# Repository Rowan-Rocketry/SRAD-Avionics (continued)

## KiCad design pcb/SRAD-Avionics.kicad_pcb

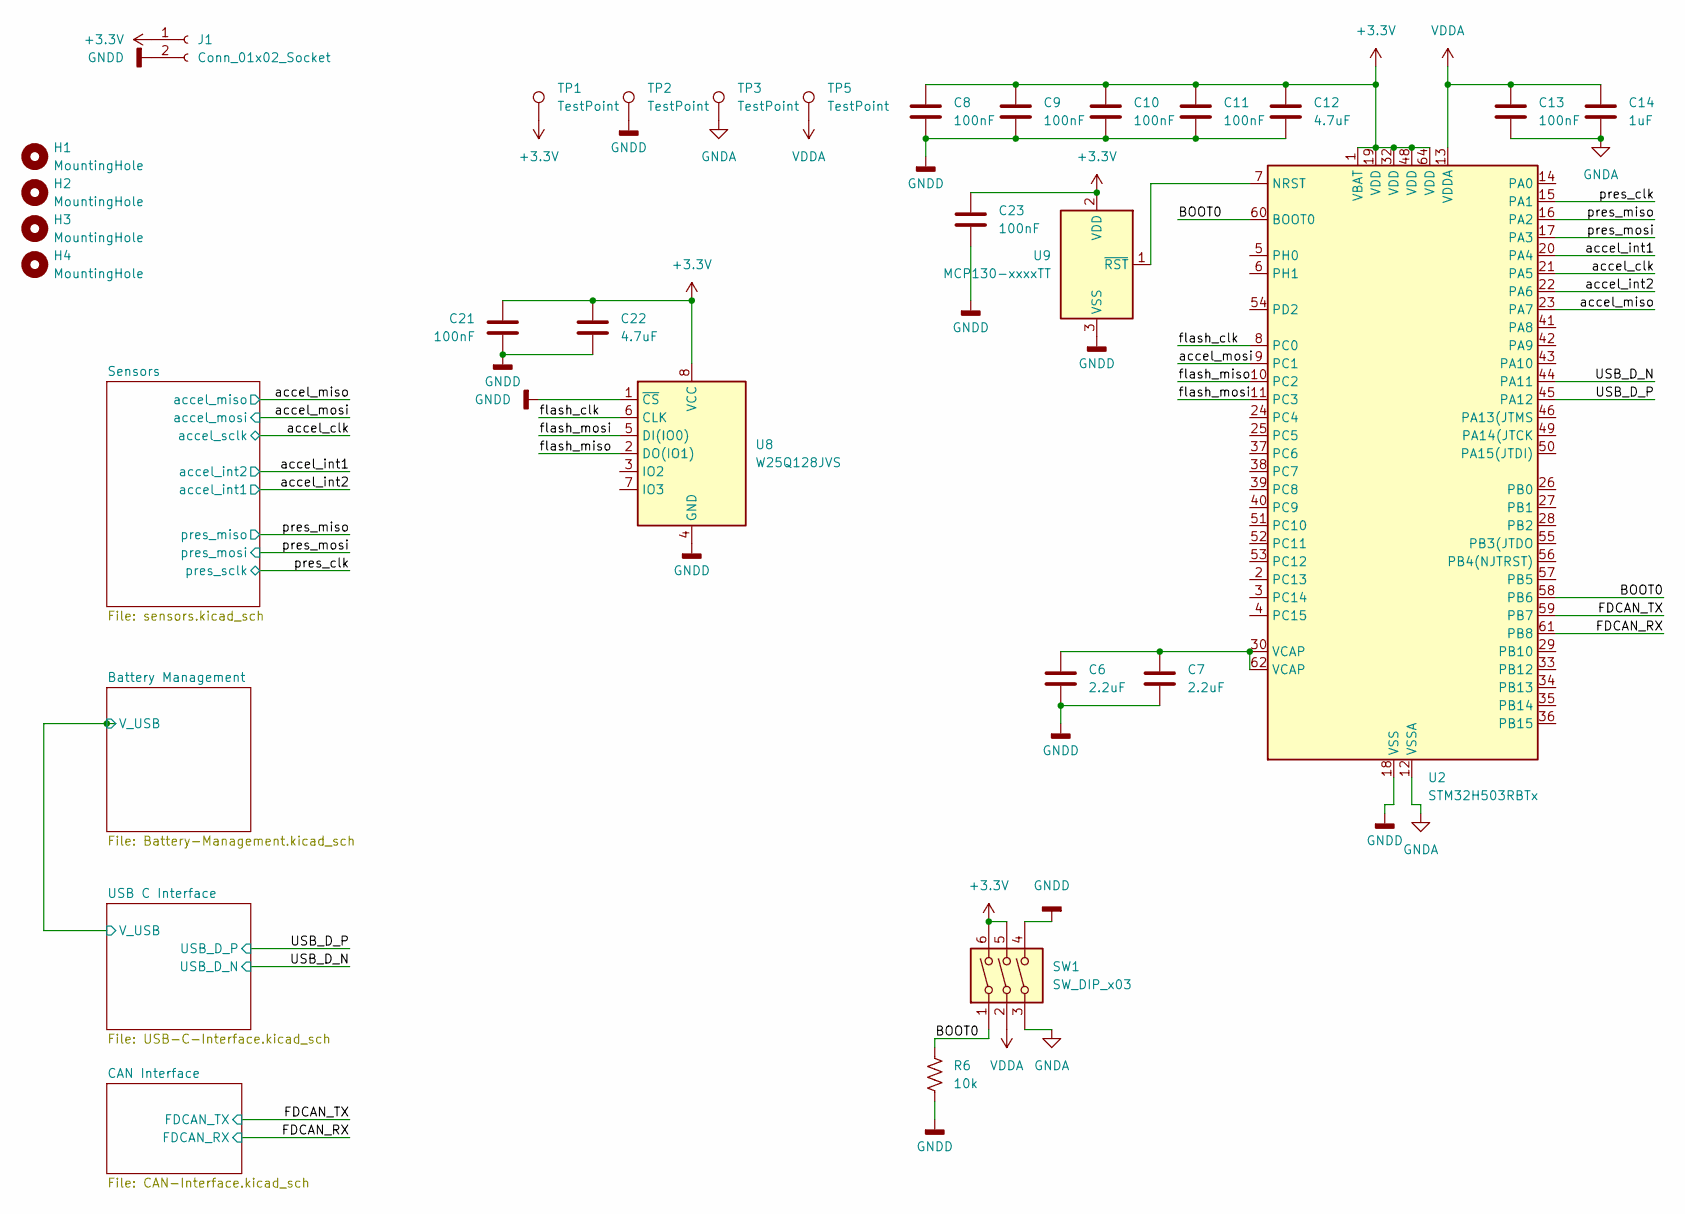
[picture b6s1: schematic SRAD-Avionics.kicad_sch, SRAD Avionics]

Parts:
C6, C7: 2.2uF; C_0603_1608Metric_Pad1.08x0.95mm_HandSolder
C8, C9, C10, C11, C13, C21, C23: 100nF; C_0603_1608Metric_Pad1.08x0.95mm_HandSolder
C12, C22: 4.7uF; C_0603_1608Metric_Pad1.08x0.95mm_HandSolder
C14: 1uF; C_0603_1608Metric_Pad1.08x0.95mm_HandSolder
H1, H2, H3, H4: MountingHole; MountingHole_3.2mm_M3
J1: Conn_01x02_Socket; TerminalBlock_Phoenix_MKDS-1,5-2-5.08_1x02_P5.08mm_Horizont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
R6: 10k; R_0603_1608Metric_Pad0.98x0.95mm_HandSolder
SW1: SW_DIP_x03; SW_DIP_SPSTx03_Slide_9.78x9.8mm_W7.62mm_P2.54mm
TP1, TP2, TP3, TP5: TestPoint; TestPoint_Loop_D2.60mm_Drill1.6mm_Beaded
U2: STM32H503RBTx; LQFP-64_10x10mm_P0.5mm
U8: W25Q128JVS; SOIC-8_5.23x5.23mm_P1.27mm
U9: MCP130-xxxxTT; SOT-23

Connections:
+3.3V: C8.1, C9.1, C10.1, C11.1, C12.1, C21.1, C22.1, C23.1, J1.1, SW1.5, SW1.6, TP1.1, U2.1 (VBAT), U2.19 (VDD), U2.32 (VDD), U2.48 (VDD), U2.64 (VDD), U8.8 (VCC), U9.2 (VDD); also elsewhere on the board
/BOOT0: R6.1, SW1.1, U2.58 (PB6), U2.60 (BOOT0)
/FDCAN_RX: U2.61 (PB8); also elsewhere on the board
/FDCAN_TX: U2.59 (PB7); also elsewhere on the board
/USB_D_N: U2.44 (PA11); also elsewhere on the board
/USB_D_P: U2.45 (PA12); also elsewhere on the board
/accel_clk: U2.21 (PA5); also elsewhere on the board
/accel_int1: U2.20 (PA4); also elsewhere on the board
/accel_int2: U2.22 (PA6); also elsewhere on the board
/accel_miso: U2.23 (PA7); also elsewhere on the board
/accel_mosi: U2.9 (PC1); also elsewhere on the board
/flash_clk: U2.8 (PC0), U8.6 (CLK)
/flash_miso: U2.10 (PC2), U8.2 (DO(IO1))
/flash_mosi: U2.11 (PC3), U8.5 (DI(IO0))
/pres_clk: U2.15 (PA1); also elsewhere on the board
/pres_miso: U2.16 (PA2); also elsewhere on the board
/pres_mosi: U2.17 (PA3); also elsewhere on the board
GNDA: C13.2, C14.2, SW1.3, TP3.1, U2.12 (VSSA)
GNDD: C6.2, C7.2, C8.2, C9.2, C10.2, C11.2, C12.2, C21.2, C22.2, C23.2, J1.2, R6.2, SW1.4, TP2.1, U2.18 (VSS), U2.31 (VSS), U2.47 (VSS), U2.63 (VSS), U8.1 (~CS), U8.4 (GND), U9.3 (VSS); also elsewhere on the board
unnamed: C6.1, C7.1, U2.30 (VCAP), U2.62 (VCAP)
unnamed: U2.7 (NRST), U9.1 (~RST)
VDDA: C13.1, C14.1, SW1.2, TP5.1, U2.13 (VDDA)

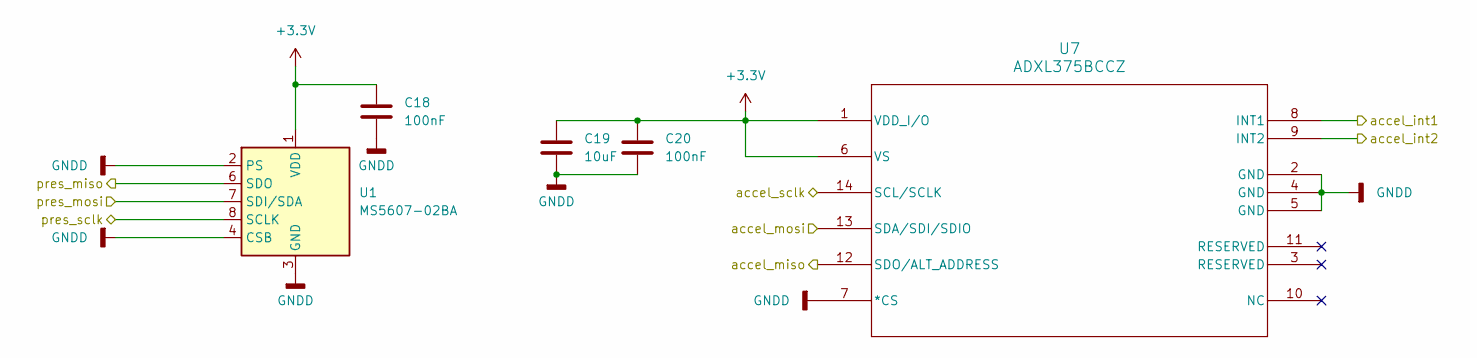
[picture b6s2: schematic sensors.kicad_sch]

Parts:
C18, C20: 100nF; C_0603_1608Metric_Pad1.08x0.95mm_HandSolder
C19: 10uF; CP_EIA-3216-18_Kemet-A_Pad1.58x1.35mm_HandSolder
U1: MS5607-02BA; LGA-8_3x5mm_P1.25mm
U7: ADXL375BCCZ; LGA-14_3x5mm_P0.8mm_LayoutBorder1x6y

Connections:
+3.3V: C18.1, C19.1, C20.1, U1.1 (VDD), U7.1 (VDD_I/O), U7.6 (VS); also elsewhere on the board
/accel_clk: U7.14 (SCL/SCLK); also elsewhere on the board
/accel_int1: U7.9 (INT2); also elsewhere on the board
/accel_int2: U7.8 (INT1); also elsewhere on the board
/accel_miso: U7.12 (SDO/ALT_ADDRESS); also elsewhere on the board
/accel_mosi: U7.13 (SDA/SDI/SDIO); also elsewhere on the board
/pres_clk: U1.8 (SCLK); also elsewhere on the board
/pres_miso: U1.6 (SDO); also elsewhere on the board
/pres_mosi: U1.7 (SDI/SDA); also elsewhere on the board
GNDD: C18.2, C19.2, C20.2, U1.2 (PS), U1.3 (GND), U1.4 (CSB), U1.5 (CSB), U7.2 (GND), U7.4 (GND), U7.5 (GND), U7.7 (*CS); also elsewhere on the board

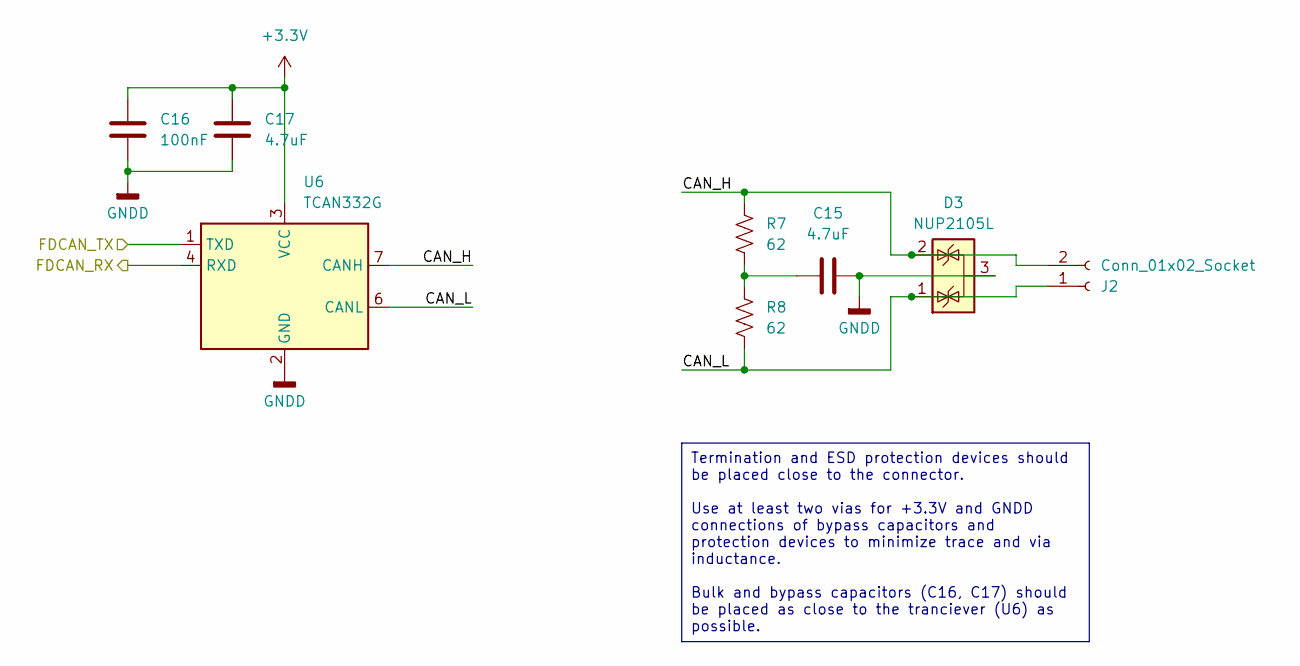
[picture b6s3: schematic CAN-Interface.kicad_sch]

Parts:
C15, C17: 4.7uF; C_0603_1608Metric_Pad1.08x0.95mm_HandSolder
C16: 100nF; C_0603_1608Metric_Pad1.08x0.95mm_HandSolder
D3: NUP2105L; SOT-23
J2: Conn_01x02_Socket; TerminalBlock_Phoenix_MKDS-1,5-2-5.08_1x02_P5.08mm_Horizont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
R7, R8: 62; R_0805_2012Metric_Pad1.20x1.40mm_HandSolder
U6: TCAN332G; SOIC-8_3.9x4.9mm_P1.27mm

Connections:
+3.3V: C16.1, C17.1, U6.3 (VCC); also elsewhere on the board
/CAN Interface/CAN_H: D3.2 (K), J2.2, R7.1, U6.7 (CANH)
/CAN Interface/CAN_L: D3.1 (K), J2.1, R8.2, U6.6 (CANL)
/FDCAN_RX: U6.4 (RXD); also elsewhere on the board
/FDCAN_TX: U6.1 (TXD); also elsewhere on the board
GNDD: C15.2, C16.2, C17.2, D3.3 (A), U6.2 (GND); also elsewhere on the board
unnamed: C15.1, R7.2, R8.1

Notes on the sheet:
Termination and ESD protection devices should be placed close to the connector. Use at least two vias for +3.3V and GNDD connections of bypass capacitors and protection devices to minimize trace and via inductance. Bulk and bypass capacitors (C16, C17) should be placed as close to the tranciever (U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

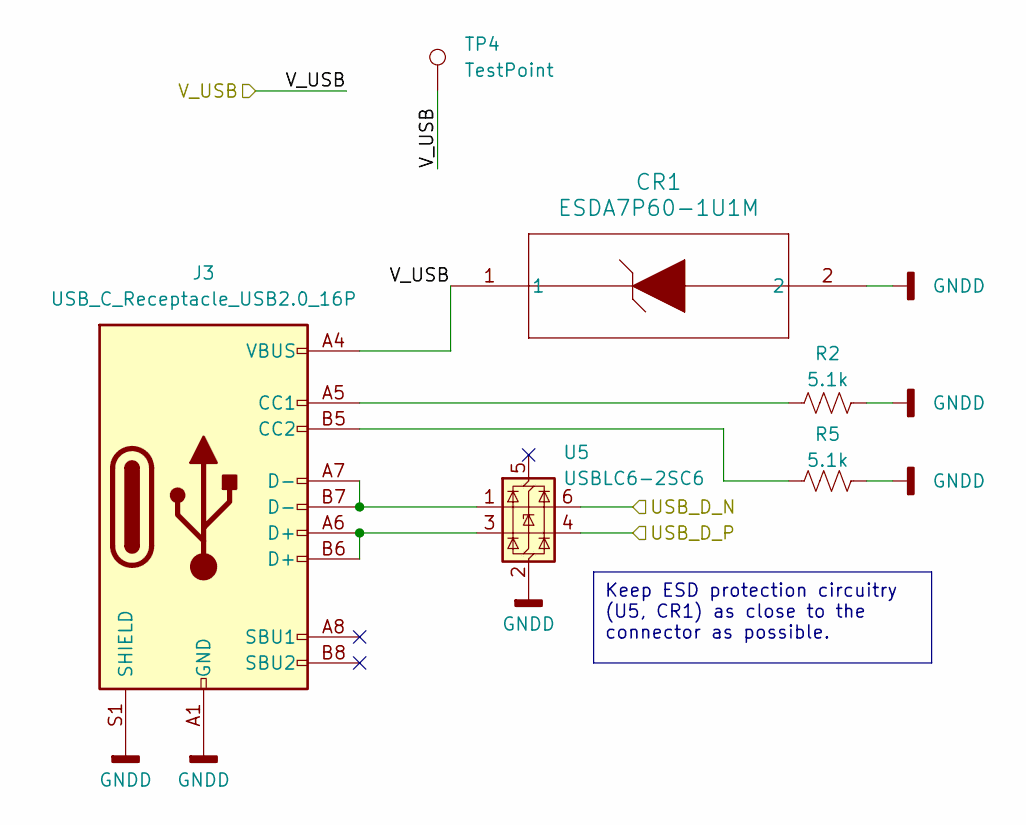
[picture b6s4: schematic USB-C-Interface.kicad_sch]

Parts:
CR1: ESDA7P60-1U1M; ZDO_1610_STM
J3: USB_C_Receptacle_USB2.0_16P; USB_C_Receptacle_GCT_USB4105-xx-A_16P_TopMnt_Horizontal
R2, R5: 5.1k; R_0603_1608Metric_Pad0.98x0.95mm_HandSolder
TP4: TestPoint; TestPoint_Loop_D2.60mm_Drill1.6mm_Beaded
U5: USBLC6-2SC6; SOT-23-6

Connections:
/Battery Management/V_USB: CR1.1, J3.A4 (VBUS), J3.A9 (VBUS), J3.B4 (VBUS), J3.B9 (VBUS), TP4.1; also elsewhere on the board
/USB_D_N: U5.6 (I/O1); also elsewhere on the board
/USB_D_P: U5.4 (I/O2); also elsewhere on the board
GNDD: CR1.2, J3.A1 (GND), J3.A12 (GND), J3.B1 (GND), J3.B12 (GND), J3.S1 (SHIELD), R2.2, R5.2, U5.2 (GND); also elsewhere on the board
unnamed: J3.A5 (CC1), R2.1
unnamed: J3.B5 (CC2), R5.1
unnamed: J3.A6 (D+), J3.B6 (D+), U5.3 (I/O2)
unnamed: J3.A7 (D-), J3.B7 (D-), U5.1 (I/O1)

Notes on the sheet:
Keep ESD protection circuitry (U5, CR1) as close to the connector as possible.

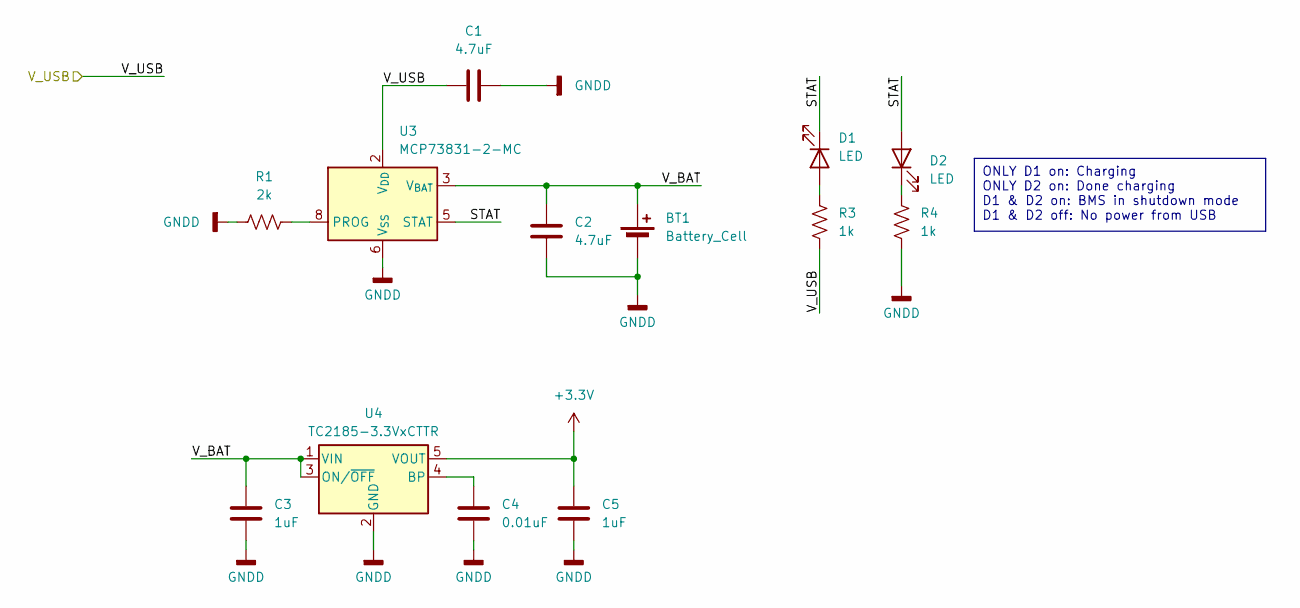
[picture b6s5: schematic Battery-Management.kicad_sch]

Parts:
BT1: Battery_Cell; BatteryHolder_MPD_BH-18650-PC2
C1, C2: 4.7uF; C_0603_1608Metric_Pad1.08x0.95mm_HandSolder
C3, C5: 1uF; C_0603_1608Metric_Pad1.08x0.95mm_HandSolder
C4: 0.01uF; C_0603_1608Metric_Pad1.08x0.95mm_HandSolder
D1, D2: LED; LED_0603_1608Metric_Pad1.05x0.95mm_HandSolder
R1: 2k; R_0603_1608Metric_Pad0.98x0.95mm_HandSolder
R3, R4: 1k; R_0603_1608Metric_Pad0.98x0.95mm_HandSolder
U3: MCP73831-2-MC; DFN-8-1EP_3x2mm_P0.5mm_EP1.7x1.4mm
U4: TC2185-3.3VxCTTR; SOT-23-5

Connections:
+3.3V: C5.1, U4.5 (VOUT); also elsewhere on the board
/Battery Management/STAT: D1.1 (K), D2.2 (A), U3.5 (STAT)
/Battery Management/V_BAT: BT1.1 (+), C2.1, C3.1, U3.3 (V_{BAT}), U3.4 (V_{BAT}), U4.1 (VIN), U4.3 (ON/~OFF)
/Battery Management/V_USB: C1.1, R3.2, U3.1 (V_{DD}), U3.2 (V_{DD}); also elsewhere on the board
GNDD: BT1.2 (-), C1.2, C2.2, C3.2, C4.2, C5.2, R1.2, R4.2, U3.6 (V_{SS}), U4.2 (GND); also elsewhere on the board
unnamed: D1.2 (A), R3.1
unnamed: D2.1 (K), R4.1
unnamed: R1.1, U3.8 (PROG)
unnamed: C4.1, U4.4 (BP)

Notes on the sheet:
ONLY D1 on: Charging ONLY D2 on: Done charging D1 & D2 on: BMS in shutdown mode D1 & D2 off: No power from USB

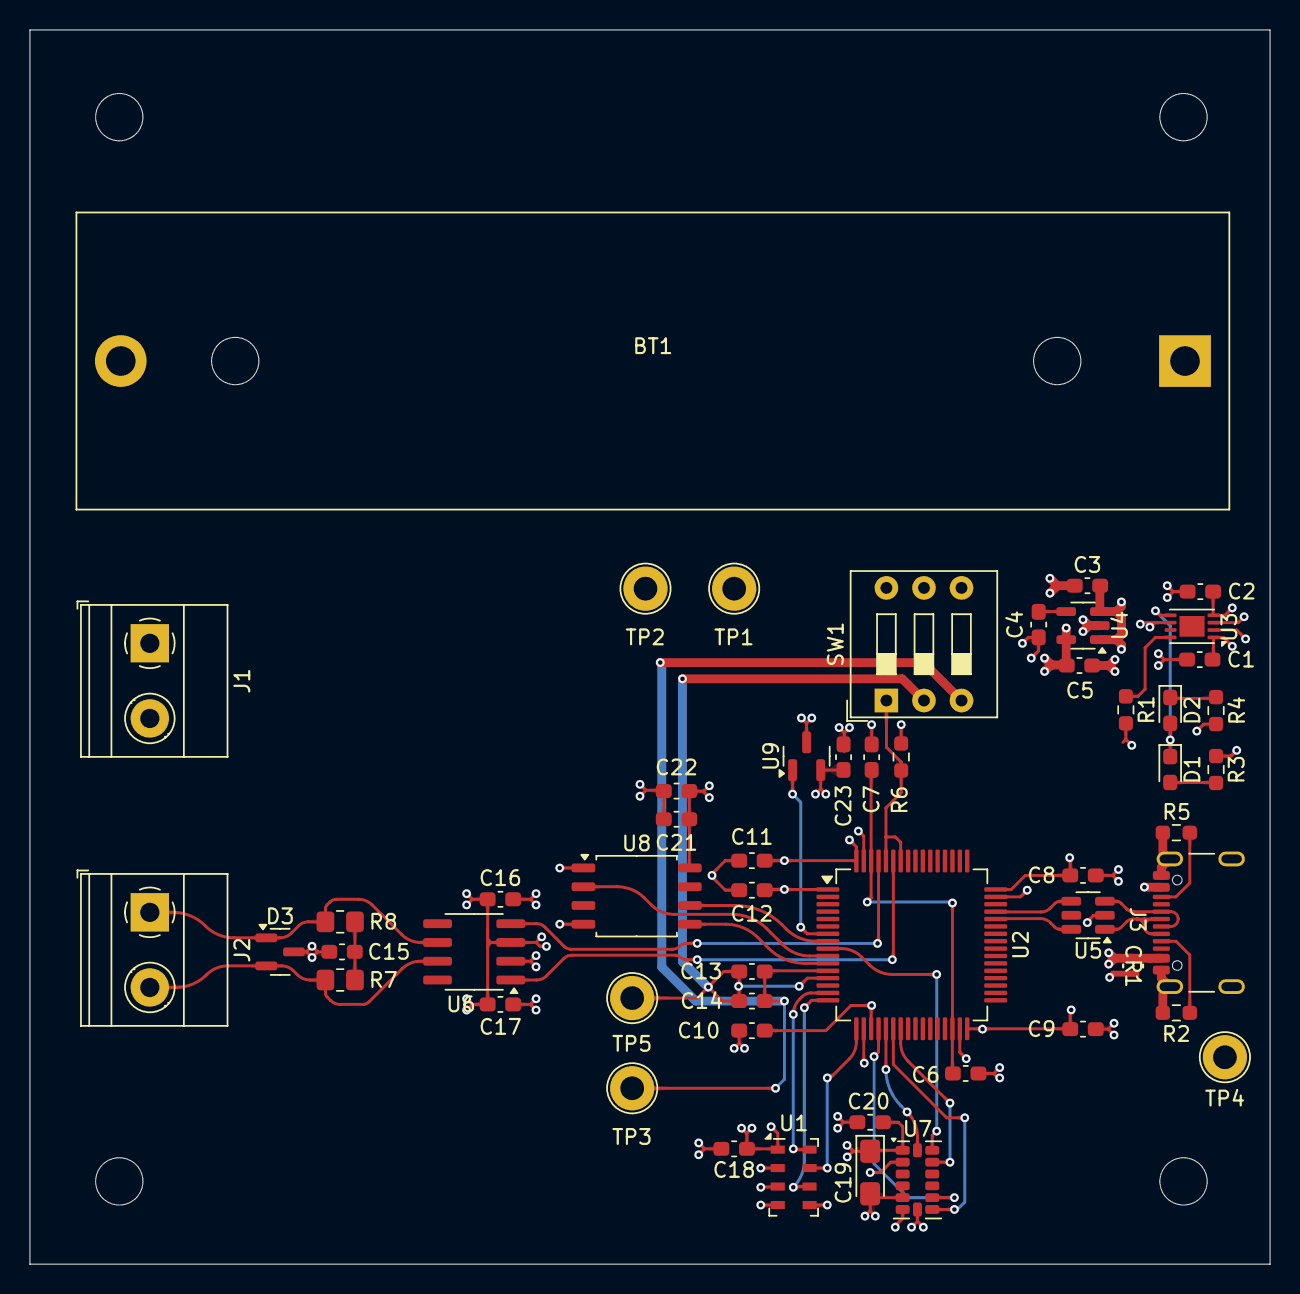
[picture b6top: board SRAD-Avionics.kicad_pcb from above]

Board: 4 copper layers, 83.9 x 83.5 mm, 58 parts (0 on the bottom side), 36 nets.

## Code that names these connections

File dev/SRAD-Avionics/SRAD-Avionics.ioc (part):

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Mcu.Name=STM32H503RBTx
Mcu.Package=LQFP64
Mcu.UserName=STM32H503RBTx
PA1.Mode=Full_Duplex_Master
PA1.Signal=SPI3_SCK
PA11.Mode=Device
PA11.Signal=USB_DM
PA12.Mode=Device
PA12.Signal=USB_DP
PA2.Mode=Full_Duplex_Master
PA2.Signal=SPI3_MISO
PA3.Mode=Full_Duplex_Master
PA3.Signal=SPI3_MOSI
PA4.GPIOParameters=GPIO_Label
PA4.GPIO_Label=accel_int1
PA4.Signal=GPIO_Input
PA5.Mode=Full_Duplex_Master
PA5.Signal=SPI2_SCK
PA6.GPIOParameters=GPIO_Label
PA6.GPIO_Label=accel_int2
PA6.Signal=GPIO_Input
PA7.Mode=Full_Duplex_Master
PA7.Signal=SPI2_MISO
PB6.GPIOParameters=GPIO_Label
PB6.GPIO_Label=USB_mode
PB6.Signal=GPIO_Input
PB7.Mode=FDCAN_Activate
PB7.Signal=FDCAN1_TX
PB8.Mode=FDCAN_Activate
PB8.Signal=FDCAN1_RX
PC0.Mode=Full_Duplex_Master
PC0.Signal=SPI1_SCK
PC1.Mode=Full_Duplex_Master
PC1.Signal=SPI2_MOSI
PC2.Mode=Full_Duplex_Master
PC2.Signal=SPI1_MISO
PC3.Mode=Full_Duplex_Master
PC3.Signal=SPI1_MOSI
RCC.HSE_VALUE=25000000
RCC.SYSCLKFreq_VALUE=32000000
board=custom

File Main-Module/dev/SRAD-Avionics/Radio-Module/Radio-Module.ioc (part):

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Mcu.Name=STM32U545RETxQ
Mcu.Package=LQFP64
Mcu.UserName=STM32U545RETxQ
PA0.Mode=Asynchronous
PA0.Signal=UART4_TX
PA1.Mode=Full_Duplex_Master
PA1.Signal=SPI1_SCK
PA11.Mode=Device
PA11.Signal=USB_DM
PA12.Mode=Device
PA12.Signal=USB_DP
PA6.Mode=Full_Duplex_Master
PA6.Signal=SPI1_MISO
PA7.Mode=Full_Duplex_Master
PA7.Signal=SPI1_MOSI
PB0.Signal=GPIO_Input
PB1.Signal=GPIO_Input
PB10.Mode=Full_Duplex_Master
PB10.Signal=SPI2_SCK
PB4\ (NJTRST).Mode=Full_Duplex_Master
PB4\ (NJTRST).Signal=SPI3_MISO
PB5.Mode=Full_Duplex_Master
PB5.Signal=SPI3_MOSI
PC1.Mode=Full_Duplex_Master
PC1.Signal=SPI2_MOSI
PC10.Mode=Full_Duplex_Master
PC10.Signal=SPI3_SCK
PC11.Mode=Asynchronous
PC11.Signal=UART4_RX
PC12.Mode=Asynchronous
PC12.Signal=UART5_TX
PC2.Mode=Full_Duplex_Master
PC2.Signal=SPI2_MISO
PD2.Mode=Asynchronous
PD2.Signal=UART5_RX
RCC.HSE_VALUE=16000000
board=custom

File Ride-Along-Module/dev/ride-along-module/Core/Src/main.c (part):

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  GPIO_InitStruct.Speed = GPIO_SPEED_FREQ_LOW;
  HAL_GPIO_Init(VALVE_FIRE_GPIO_Port, &GPIO_InitStruct);

  /*Configure GPIO pins : PYRO1_FIRE_Pin PH1 and IMU_CS *//////////////////
  GPIO_InitStruct.Pin = PYRO1_FIRE_Pin|GPIO_PIN_1;
  GPIO_InitStruct.Mode = GPIO_MODE_OUTPUT_PP;
  GPIO_InitStruct.Pull = GPIO_NOPULL;
  GPIO_InitStruct.Speed = GPIO_SPEED_FREQ_LOW;
  HAL_GPIO_Init(GPIOH, &GPIO_InitStruct);

  /*Configure GPIO pins : IMU_INT1_Pin IMU_INT2_Pin *//////////////////////////
  GPIO_InitStruct.Pin = IMU_INT1_Pin|IMU_INT2_Pin;
  GPIO_InitStruct.Mode = GPIO_MODE_IT_RISING;
  GPIO_InitStruct.Pull = GPIO_NOPULL;
  HAL_GPIO_Init(GPIOC, &GPIO_InitStruct);

  /*Configure GPIO pins : PYRO2_FIRE_Pin PA2 and PRES_CS*/
  GPIO_InitStruct.Pin = PYRO2_FIRE_Pin|GPIO_PIN_3;
  GPIO_InitStruct.Mode = GPIO_MODE_OUTPUT_PP;
  GPIO_InitStruct.Pull = GPIO_NOPULL;
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  GPIO_InitStruct.Mode = GPIO_MODE_IT_RISING;
  GPIO_InitStruct.Pull = GPIO_NOPULL;
  HAL_GPIO_Init(PYRO1_ADC_Port, &GPIO_InitStruct);
  /*Configure GPIO pins : PYRO2_ADC_Pin PA1 *///////////////////////////////////
  GPIO_InitStruct.Pin = PYRO2_ADC_Pin;
  GPIO_InitStruct.Mode = GPIO_MODE_IT_RISING;
  GPIO_InitStruct.Pull = GPIO_NOPULL;
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	log_status("INFO", "LSM6DSL data ready");
	switch (gpioPin)
	{
		case IMU_INT1_Pin:
			//LSM6DSL_updateAccel();
		case IMU_INT2_Pin:
			//LSM6DSL_updateGyro();
	}
}
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//	  	log_status("INFO", "PYRO1 Set LOW");
//
//	  	////////////////////////Pyro 2
//	  	HAL_Delay(1000); //Pyro02 Fire = PA2, ADCin2 = PA1
//		HAL_GPIO_WritePin(PYRO2_FIRE_GPIO_Port, PYRO2_FIRE_Pin, GPIO_PIN_SET);
//		log_status("INFO", "PYRO2 Set HIGH");
//		// Get ADC value
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
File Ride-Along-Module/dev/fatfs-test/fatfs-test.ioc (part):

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Mcu.Name=STM32L4R9Z(G-I)Tx
Mcu.Package=LQFP144
Mcu.UserName=STM32L4R9ZGTx
PC10.Mode=SD_4_bits_Wide_bus
PC10.Signal=SDMMC1_D2
PC11.Mode=SD_4_bits_Wide_bus
PC11.Signal=SDMMC1_D3
PC12.Mode=SD_4_bits_Wide_bus
PC12.Signal=SDMMC1_CK
PC8.Mode=SD_4_bits_Wide_bus
PC8.Signal=SDMMC1_D0
PC9.Mode=SD_4_bits_Wide_bus
PC9.Signal=SDMMC1_D1
PD2.Mode=SD_4_bits_Wide_bus
PD2.Signal=SDMMC1_CMD
RCC.HSE_VALUE=8000000
board=custom

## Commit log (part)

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2024-07-07 Started PCB project
2024-07-09 New microcontroller (STM32H503RBT6) and new GPS module (MAX-8C)
2024-07-14 Finished schematics for battery charging and output voltage regulation
2024-07-17 Added USB C and CAN interfaces to schematic
2024-07-17 New, simpler CAN interface that supports FD CAN
2024-07-18 Routed USB interface from port to MCU and CAN interface from connector to transceiver
2024-07-21 New dir structure. USB, CAN, power layout done. Started CubeIDE project
2024-07-22 Routed reset monitor, all test points, 128 MBit flash, sensors, analog-digital jumper switches
2024-07-28 New, module-based directory tree, new CAN bus connector on main module, separate battery board, pin header for board stacking
2024-07-29 New board edge cuts defined in CAD
2024-08-21 Minor routing changes
2024-08-22 Added footprints for GPS module, new edge cuts for main module
2024-09-17 Folders and pcb creation
    Created valve-module pcb project.
2024-09-17 Created Pyro-Module PCB project
2024-09-19 Main-module pcb
    Added in copy of Main-module pcb.
2024-09-19 Coppied PCB File to GPS Module
2024-09-19 Added PCB file to pyro module
2024-09-19 Created valve-module.ioc
    created new valve-module.ioc within the dev folder
2024-09-19 Created STM32 Project
2024-09-19 STM32 Project
2024-09-26 Added in schematic
    Added schematic for main
2024-09-26 Deleted un needed files (duplicate)
2024-09-26 Updated valve files for main
    Added in additional files for schematic
2024-09-26 Deleted Can interface from Radio Module
2024-09-26 Created microcontroller schematic
2024-09-27 Created common microcontroller schematic
2024-10-01 Created Recovery Module from Valve Module
2024-10-01 Renamed GPS Module PCB files to Radio Module
2024-10-01 Set up base directory structure for three-board branch
2024-10-01 Created flash schematic
2024-10-01 Updated Schematic
    USBC, Sensor, MCU
2024-10-01 Added Valve Controller and Pyro Controller to Block Diagram
2024-10-01 Updating Schematics
2024-10-01 Added Pyro Controller and Valve Controller to Block Diagram
2024-10-01 Made Apogee Input
2024-10-03 Worked on Radio Transciever
2024-10-07 Finished radio module
2024-10-08 Root page changes
2024-10-08 Made MC more generic
2024-10-08 Draft of valve schematic
    without load resistor and mosfet, waiting for valve to be ordered
2024-10-17 Valve Schematic Update
2024-10-17 Started Pyro Controller Sch.
2024-10-17 Updated Pyro Controller Sch. in LTSpice
2024-10-17 Created Project
2024-10-17 deleted old modules
2024-10-17 Deleted Extra Pyro Controller Folder
2024-10-17 Revert "Root page changes"
    This reverts commit 37496c938203c7bb6b12bb47924aa7949687527b.
2024-10-17 Adjusted LSpice Sim Valve
2024-10-17 Slight change pins
2024-10-17 slight change to top level
2024-10-22 Added Pyro Controller Sch.
2024-10-22 Changes to Pyro Schematic
    Footprint Changes
2024-10-22 Initial Layout for Pyro Controller
2024-10-24 Picked new (singular) nMOS for pyro controller. Finished board routing.
2024-10-24 Added testpoint to Pyro Controller
2024-10-24 Fixed Oscillator and SMA Connector for radio module
2024-10-24 Pyro controller routing for pick and place.
2024-10-24 Added fiducials and repositioned the reference designators.
2024-10-24 Finished fiducials, added title and revision
2024-10-29 Created STM32L052C8 schematic in Common
2024-10-29 Updated Common Microcontroller Schematic
2024-10-29 Updated BOM for Pyro Controller Board
2024-10-29 Converted csv BOM to xlsx file
2024-10-29 Common MCU Update
2024-10-30 BOM, BOM Template, Rowan Rocketry Logo
    - Finished pyro controller BOM
    - Created template for BOMs
    - Created a footprint for adding the Rowan Rocketry logo to PCBs
2024-10-30 Fiducial schematic symbols. Position, gerber, and drill files generation
2024-10-31 VDD Capacitors
2024-10-31 Added New MCU to Radio Schematic
2024-11-05 Pyro Controller Rev. 1 Release
2024-11-07 Copied all Pyro-Controller schematic and pcb files to Valve-Controller Folder.
2024-11-08 Valve controller diode
2024-11-08 Updated Valve Controller PCB and BOM
2024-11-14 Create Bitstuffing Test Code
2024-11-21 Updated IMU schematic
2024-11-27 Schematic for STM32U545RE
2024-12-17 Fixed connector pitch (now 2.54mm) on pyro and valve controllers
2024-12-17 Revert "Merge pull request #15 from Rowan-Rocketry/recovery-dev"
    This reverts commit b1b375488d1c86cf0dfe83b18f6d9b8629348329, reversing
    changes made to 404c392b771be84661a253412841db10f6c9638a.
2024-12-17 Revert "Resolved recovery dev merge"
    This reverts commit 81c4bbda93894cf9b120906f02d3dbab6bbd1e60, reversing
    changes made to 220360569fc6c62025a0e7a68270d7f77f4a1f37.
2024-12-17 Fixed valve controller pin socket. Now 2.54mm pitch
2024-12-17 Resolved valve controller merge
2024-12-17 Resized pin socket pitch to 2.54mm
2024-12-17 Revert "Resolved valve controller merge"
    This reverts commit 7e28f5f88a62916d9e6a1e81675edc88063ce629.
2024-12-17 revert
2024-12-17 Revert "Schematic for STM32U545RE"
    This reverts commit e505d12bdbbff2a833c7e8d3cdd5c43ed4e68164.
2024-12-17 New gitignore
2024-12-17 removed stupid valve backup folder
2024-12-17 Revert "Fixed connector pitch (now 2.54mm) on pyro and valve controllers"
    This reverts commit cc5feacbc4d72d2d58a97731654cbbc976ceb90c.
2024-12-17 Reapply "Fixed connector pitch (now 2.54mm) on pyro and valve controllers"
    This reverts commit 2221178c5ae9715753d881bb73d0f25c579b9747.
2024-12-17 Reapply "Merge pull request #15 from Rowan-Rocketry/recovery-dev"
    This reverts commit 3181b86a9d633abc1e40c06630dfd886575f02b2.
2024-12-17 Reapply "Schematic for STM32U545RE"
    This reverts commit 3e560c947ea94282137d36b3379e7f3cf8a53679.
2024-12-17 Revert "Reapply "Schematic for STM32U545RE""
    This reverts commit 2d27b28795118751a733e088b9e563edf5cfbc3e.
2025-01-23 1/23/25
2025-01-27 last semester changes
2025-02-12 Finished IMU Rev 1
2025-02-12 IMU Rev 1 passing DRC
2025-03-05 USB C breadboard supply passing DRC
2025-03-06 USB-C PD Controller finishing touches
2025-03-06 Updated IMU board to KiCAD 9.0
2025-03-06 Updated Pyro Controller to KiCAD 9.0
2025-03-06 Updated Valve Controller to KiCAD 9.0
2025-03-07 USB-C PD Controller fabrication outputs
2025-03-30 USB-C PD controller modifications because I can't make up my mind
2025-03-30 KiCAD schematic blocks are a thing now
2025-03-30 Ride along module progress (for safety)
2025-03-31 More reuse blocks. Added battery circuit to ride along board
2025-04-09 IMU test board rev 2
2025-04-09 Poll pressure measurements from MS5607 using SPI
2025-04-10 Ride-Along Module Rev. 1
2025-04-15 Pos file for IMU rev 2
2025-04-17 Timer-based MS5607 library building successfully
2025-04-19 Integrated FatFs and SD card driver support
2025-04-21 Successfully building with timestamps in ms
2025-04-23 Better sensor configuration
2025-04-23 Fixed clock power setting issue. Thanks Chat!
2025-04-23 Successfully talking to SD card. Still working out mounting file system.
2025-04-24 Fixed drill origin and generated new pos file
2025-04-24 Building with fatfs included
2025-04-30 SD-Card-Test has working code. Writing to sd card!
2025-09-11 Syncing up!
2025-09-16 Upload Ground Station files
2025-09-23 2026 Ground Station Folder
2025-09-25 Added dual ESP comms code
    Flash transmit to transmitting esp
    Flash receive to receiving esp
    Build and launch visual studio program
2025-09-30 Create windows desktop
2025-10-09 removing outdated ground station 2026 folder
2025-10-16 Display python code
2026-02-26 Kalman Filter
2026-03-02 Kalman Filter Cpp to C
2026-03-05 Kalman Filter Python Code
2026-03-05 Adjust Kalman filter parameters for closer sensor tracking
2026-03-10 Kalman Filter Python Script
2026-03-12 Kalman Filter updates
    Wowowowowow
2026-03-26 Kalman Filter 3/26
2026-03-26 Working Kalman Filter
    It actually works now with a CSV!
2026-03-31 Code changes for Rev1
    These got Rev1 working, used on L2 flight 3/28/26
2026-04-13 Added Radio-module App for GPS-test implementation
2026-04-13 Revert "Added Radio-module App for GPS-test implementation"
    This reverts commit 02f1cb2777dad3ad3a5ef724c25b838c03db3bf7.
2026-04-13 Add GPS test Radio App project folder
